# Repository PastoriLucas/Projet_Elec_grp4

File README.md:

# Projet d'électronique - Groupe 4

Dans le cadre du cours d'électronique digitale et analyse des signaux, nous avons créé un télémètre à ultrasons utilisant un PIC.
En plus de cela, nous utilisons une application Java pour avoir une interface graphique ainsi que pour pouvoir modifier le seuil de déclanchement d'alerte auprès du PIC.

Le rapport ainsi que les schémas Eagle et Proteus se trouvent dans l'onglet "Wiki".

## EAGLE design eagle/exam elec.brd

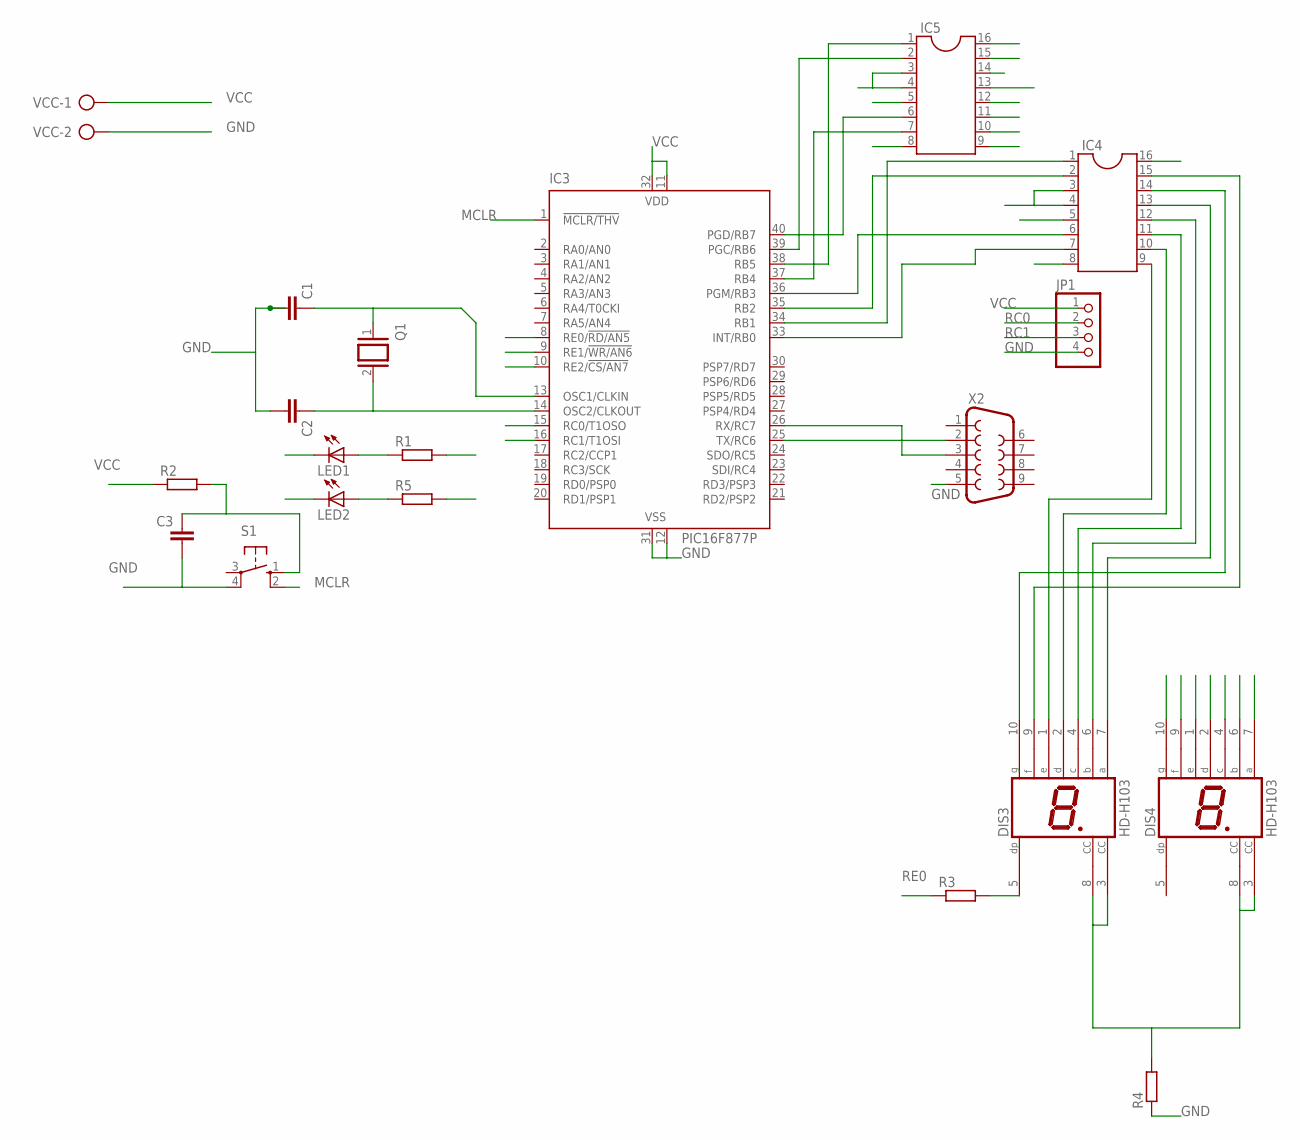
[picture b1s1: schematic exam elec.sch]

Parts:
C1, C2, C3: C-EU025-025X050; C025-025X050
DIS3, DIS4: HD-H103; HDSP-M
IC3: PIC16F877P; DIL40
IC4, IC5: DIL16
JP1: PINHD-1X4; 1X04
LED1, LED2: LED5MM
Q1: XTAL/S; QS
R1, R2, R3, R4, R5: R-EU_0204/7; 0204/7
S1: 10-XX; B3F-10XX
VCC: AK300/2
X2: F09H

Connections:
A: DIS4.7 (A), IC5.13
B: DIS4.6 (B), IC5.12
C: DIS4.4 (C), IC5.11
D: DIS4.2 (D), IC5.10
E: DIS4.1 (E), IC5.9
F: DIS4.9 (F), IC5.15
G: DIS4.10 (G), IC5.14
GND: C1.2, C2.2, C3.2, IC3.12 (VSS), IC3.31 (VSS), IC4.5, IC4.8, IC5.5, IC5.8, JP1.4, LED1.K (C), LED2.K (C), R4.1, S1.4 (P1), VCC.2, X2.5
MCLR: IC3.1 (!MCLR/THV), S1.2 (S1)
unnamed: IC3.33 (INT/RB0), IC4.7
unnamed: C1.1, IC3.13 (OSC1/CLKIN), Q1.1
unnamed: C2.1, IC3.14 (OSC2/CLKOUT), Q1.2
unnamed: IC3.34 (RB1), IC4.1
unnamed: IC3.35 (RB2), IC4.2
unnamed: IC3.25 (TX/RC6), X2.2
unnamed: IC3.26 (RX/RC7), X2.3
unnamed: IC3.36 (PGM/RB3), IC4.6
unnamed: IC3.37 (RB4), IC5.7
unnamed: IC3.38 (RB5), IC5.1
unnamed: IC3.39 (PGC/RB6), IC5.2
unnamed: IC3.40 (PGD/RB7), IC5.6
unnamed: DIS3.1 (E), IC4.9
unnamed: DIS3.2 (D), IC4.10
unnamed: DIS3.4 (C), IC4.11
unnamed: DIS3.6 (B), IC4.12
unnamed: DIS3.7 (A), IC4.13
unnamed: DIS3.10 (G), IC4.14
unnamed: DIS3.9 (F), IC4.15
unnamed: DIS3.3 (CC), DIS3.8 (CC), DIS4.3 (CC), DIS4.8 (CC), R4.2
unnamed: DIS3.5 (DP), R3.2
unnamed: C3.1, R2.2, S1.1 (S)
unnamed: LED2.A, R5.1
unnamed: LED1.A, R1.1
RC0: IC3.15 (RC0/T1OSO), JP1.2
RC1: IC3.16 (RC1/T1OSI), JP1.3
RE0: IC3.8 (RE0/!RD/AN5), R3.1
RE1: IC3.9 (RE1/!WR/AN6), R1.2
RE2: IC3.10 (RE2/!CS/AN7), R5.2
VCC: IC3.11 (VDD), IC3.32 (VDD), IC4.3, IC4.4, IC4.16, IC5.3, IC5.4, IC5.16, JP1.1, R2.1, VCC.1

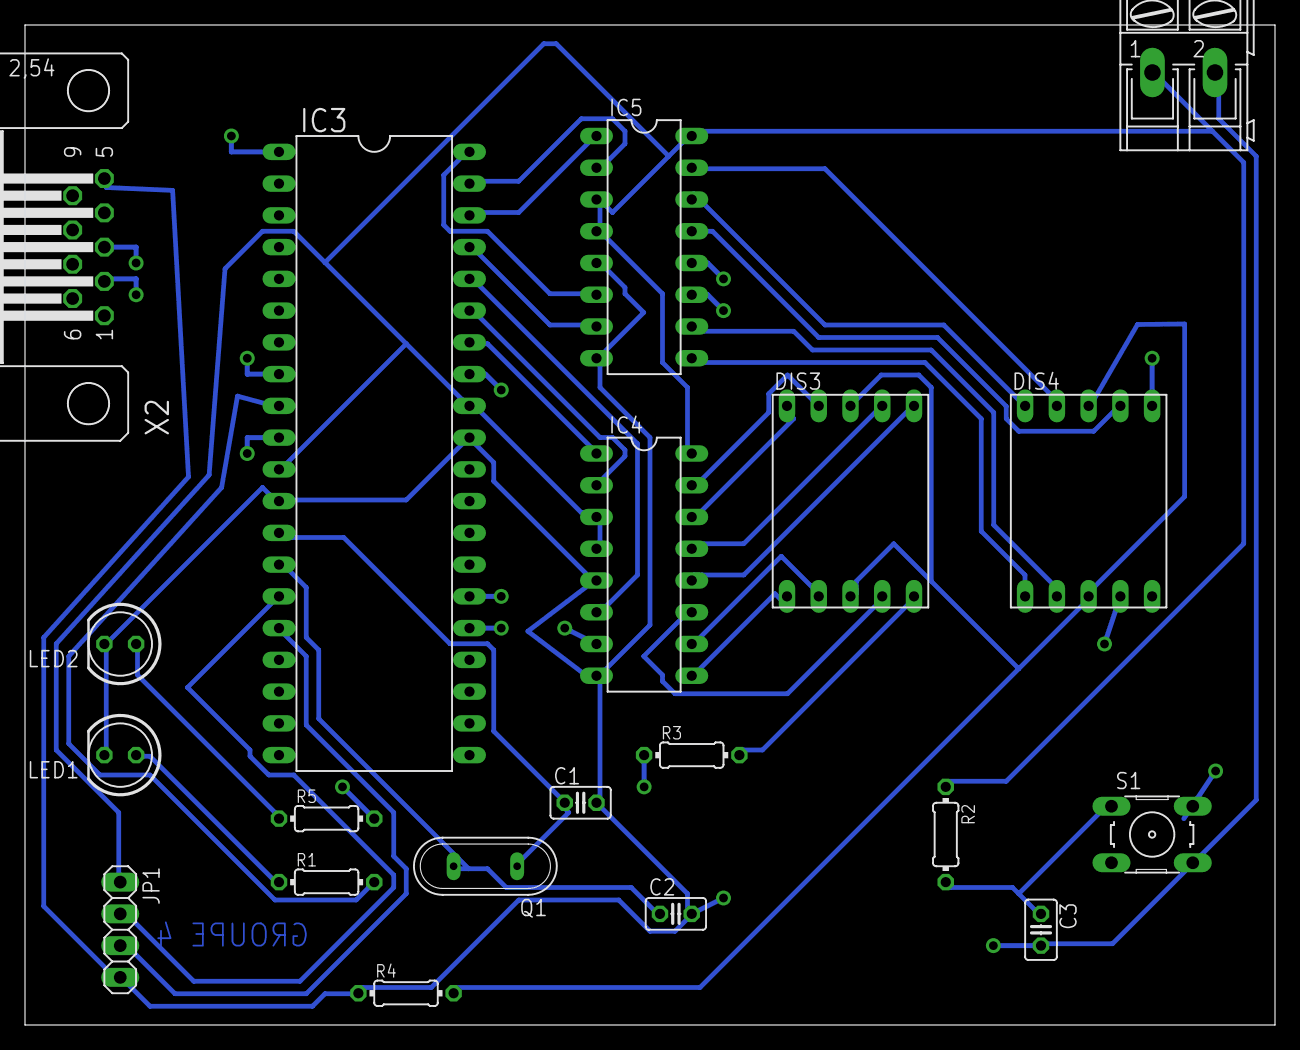
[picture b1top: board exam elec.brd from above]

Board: 2 copper layers, 100.0 x 80.0 mm, 20 parts (0 on the bottom side), 39 nets.

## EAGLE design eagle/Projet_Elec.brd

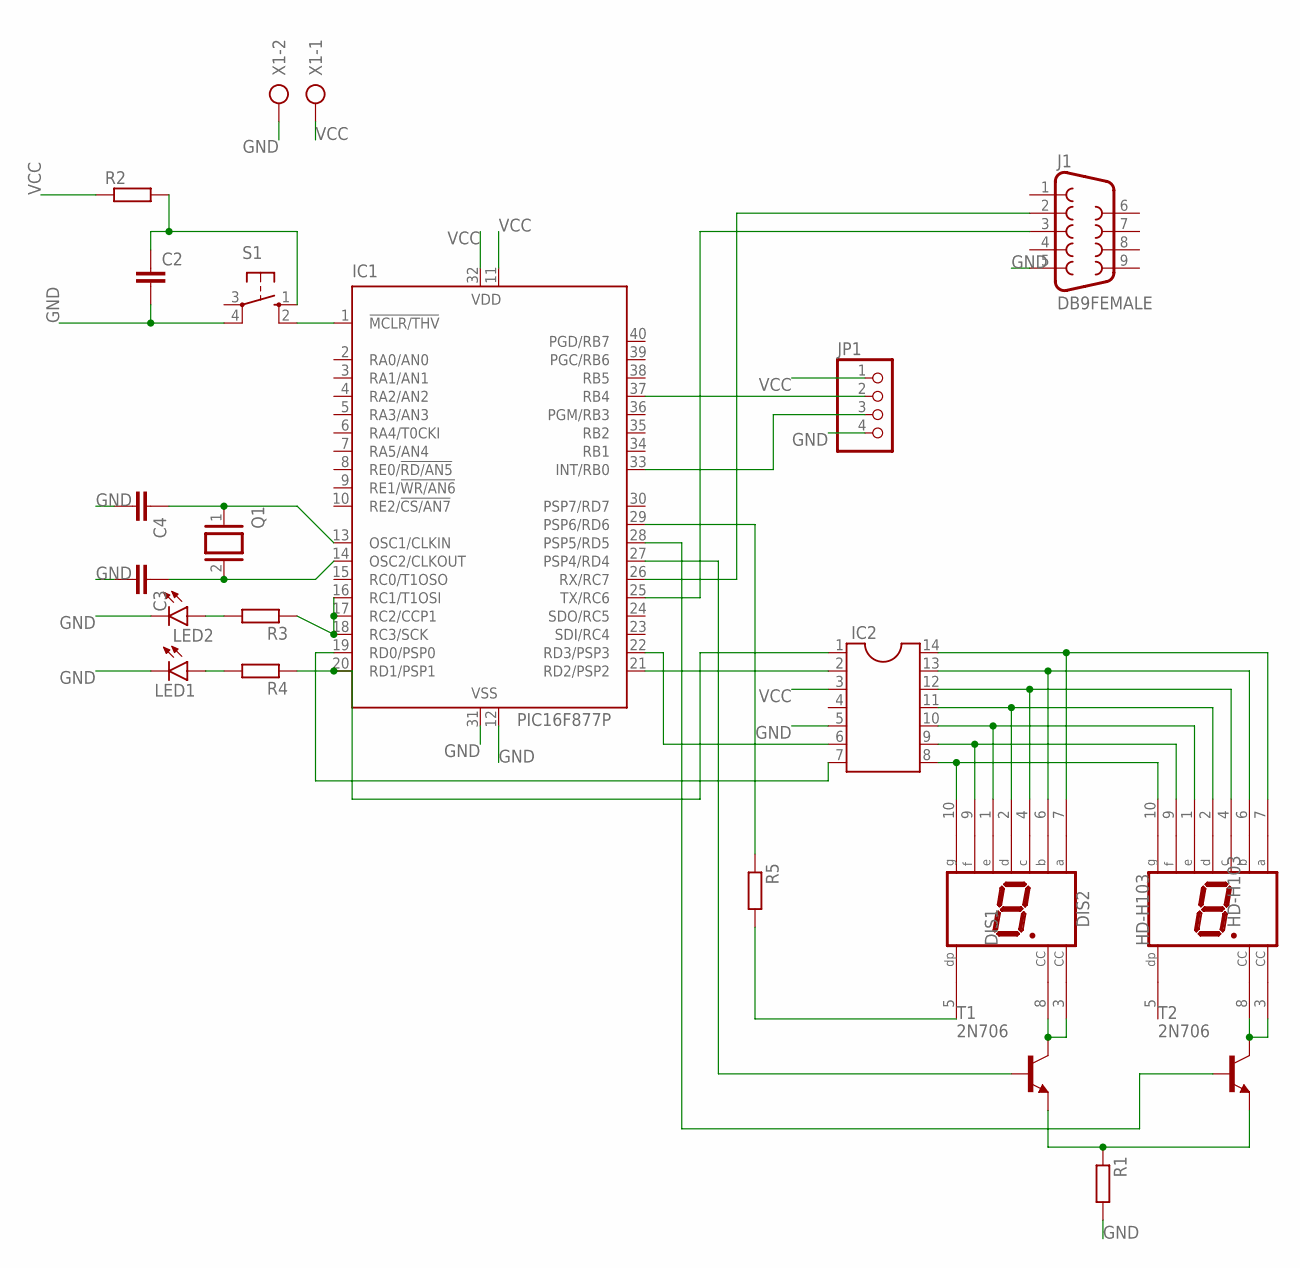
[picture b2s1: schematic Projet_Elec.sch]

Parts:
C2, C3, C4: C-EU025-024X044; C025-024X044
DIS1, DIS2: HD-H103; HDSP-M
IC1: PIC16F877P; DIL40
IC2: DIL14
J1: DB9FEMALE; DB9
JP1: PINHD-1X4; 1X04
LED1, LED2: LED5MM
Q1: XTAL/S; QS
R1, R2, R3, R4, R5: R-EU_0204/7; 0204/7
S1: 10-XX; B3F-10XX
T1, T2: 2N706; TO18
X1: AK300/2

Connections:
GND: C2.2, C3.2, C4.2, IC1.12 (VSS), IC1.31 (VSS), IC2.5, J1.5, JP1.4, LED1.K (C), LED2.K (C), R1.2, S1.4 (P1), X1.2
unnamed: IC1.1 (!MCLR/THV), S1.2 (S1)
unnamed: C2.1, R2.2, S1.1 (S)
unnamed: C4.1, IC1.13 (OSC1/CLKIN), Q1.1
unnamed: C3.1, IC1.14 (OSC2/CLKOUT), Q1.2
unnamed: IC1.16 (RC1/T1OSI), IC1.17 (RC2/CCP1), IC1.18 (RC3/SCK), R3.1
unnamed: LED2.A, R3.2
unnamed: IC1.20 (RD1/PSP1), IC2.1, R4.1
unnamed: LED1.A, R4.2
unnamed: IC1.26 (RX/RC7), J1.2
unnamed: IC1.25 (TX/RC6), J1.3
unnamed: IC1.19 (RD0/PSP0), IC2.7
unnamed: DIS1.7 (A), DIS2.7 (A), IC2.14
unnamed: DIS1.6 (B), DIS2.6 (B), IC2.13
unnamed: DIS1.4 (C), DIS2.4 (C), IC2.12
unnamed: DIS1.2 (D), DIS2.2 (D), IC2.11
unnamed: DIS1.1 (E), DIS2.1 (E), IC2.10
unnamed: DIS1.10 (G), DIS2.10 (G), IC2.8
unnamed: DIS1.3 (CC), DIS1.8 (CC), T1.3 (C)
unnamed: IC1.37 (RB4), JP1.2
unnamed: IC1.27 (PSP4/RD4), T1.2 (B)
unnamed: IC1.28 (PSP5/RD5), T2.2 (B)
unnamed: IC1.22 (RD3/PSP3), IC2.6
unnamed: R1.1, T1.1 (E), T2.1 (E)
unnamed: IC1.29 (PSP6/RD6), R5.1
unnamed: DIS1.5 (DP), R5.2
unnamed: DIS1.9 (F), DIS2.9 (F), IC2.9
unnamed: IC1.21 (RD2/PSP2), IC2.2
unnamed: IC1.33 (INT/RB0), JP1.3
unnamed: DIS2.3 (CC), DIS2.8 (CC), T2.3 (C)
VCC: IC1.11 (VDD), IC1.32 (VDD), IC2.3, JP1.1, R2.1, X1.1

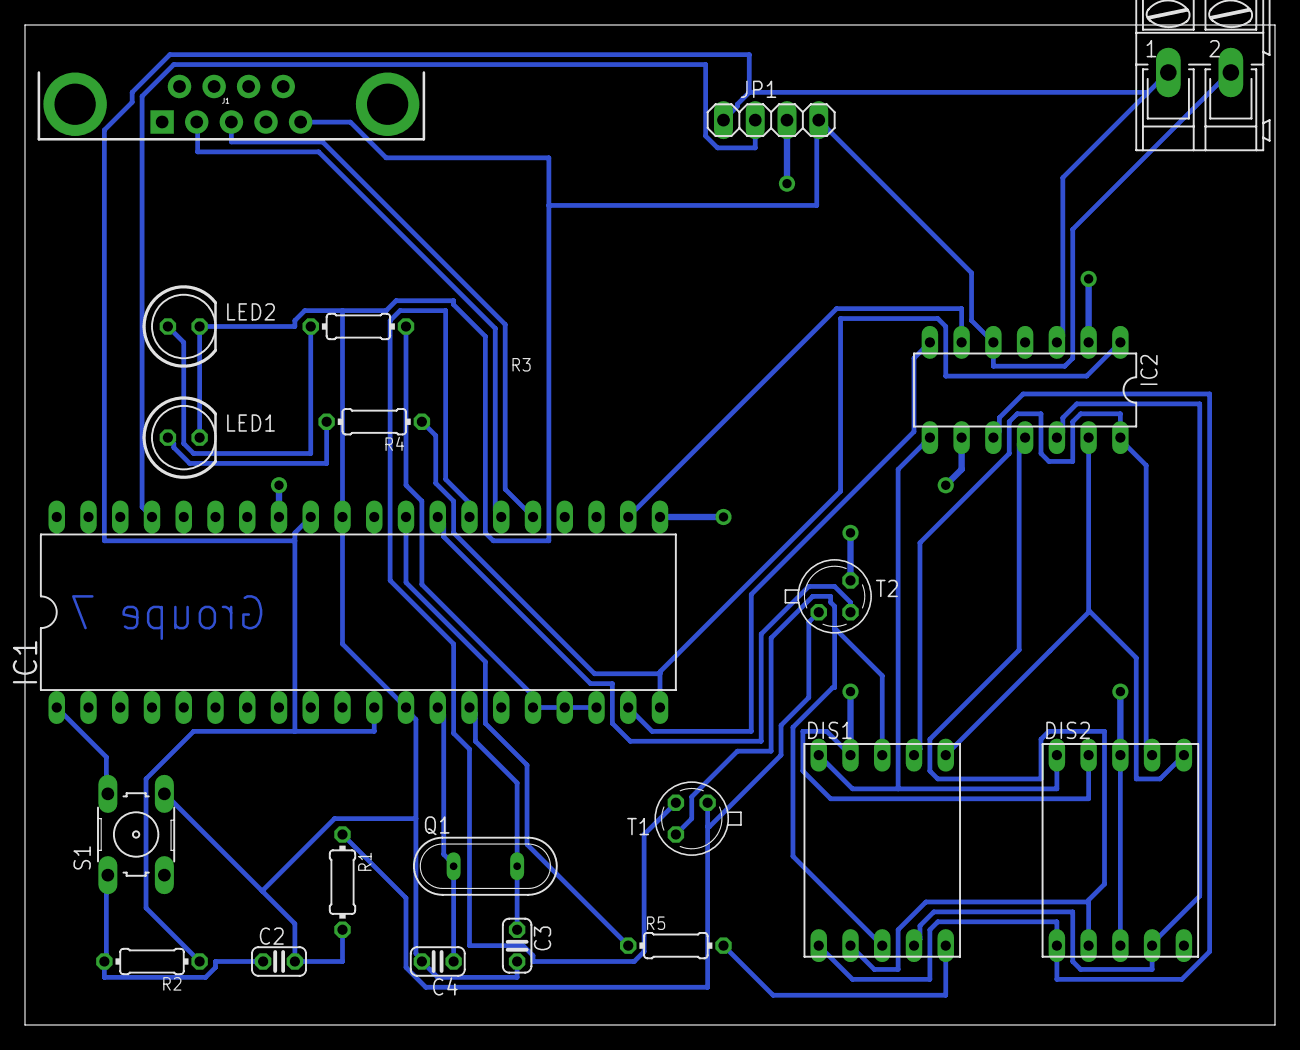
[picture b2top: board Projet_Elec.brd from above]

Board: 2 copper layers, 100.0 x 80.0 mm, 21 parts (0 on the bottom side), 31 nets.

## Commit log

2020-05-02 push java environment
    test push java environment
2020-05-02 code JAVA + gui
2020-05-03 MVC en place
2020-05-04 Avancement view
2020-05-04 View finie + debut controller
2020-05-04 Auto stash before rebase of "refs/heads/master"
2020-05-04 commit save
2020-05-04 Continuité du Controleur
2020-05-04 commit quotidien
2020-05-04 Recherche + Affichage des ports COMs
2020-05-05 Lecture sur port
2020-05-06 Lecture sur Port Com ok
2020-05-07 Code C + Proteus
2020-05-07 ajout eagle
    ajout eagle
2020-05-07 JAVA 100% fonctionnel
    Merci Taha
2020-05-07 Correction merge
2020-05-08 test
    test
2020-05-08 Début sendData
2020-05-09 envoiData
2020-05-09 avancement
2020-05-09 test
2020-05-09 merge
2020-05-09 Essai receive
2020-05-09 Commit un peu inutile
2020-05-09 version presque final
    wallah
2020-05-09 metadata
2020-05-09 Receive okk
2020-05-10 Suppr dossiers de trop
2020-05-10 Mise en forme
2020-05-10 Code commenté et terminé
2020-05-10 avant fin
2020-05-10 bon Eagle
    remplacement des mauvais schéma
2020-05-10 push .jar
2020-05-10 Finalisation C et Java
